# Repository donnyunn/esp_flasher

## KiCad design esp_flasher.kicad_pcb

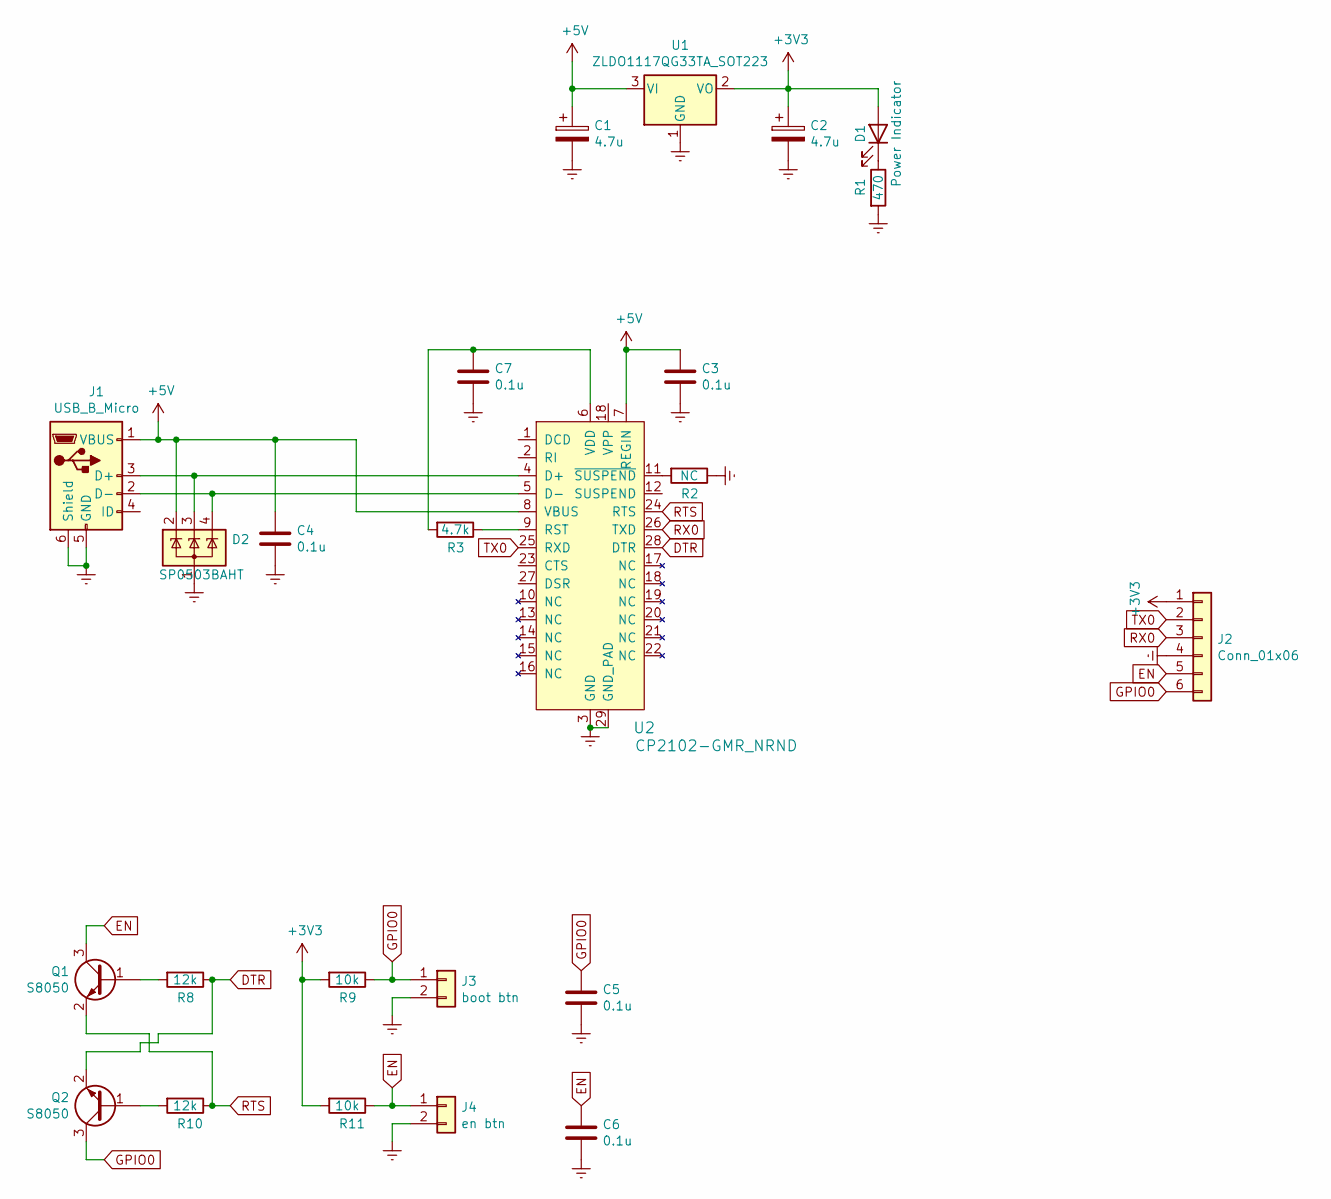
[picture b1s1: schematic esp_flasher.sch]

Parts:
C1, C2: 4.7u; CP_EIA-3216-18_Kemet-A
C3, C4, C5, C6, C7: 0.1u; C_0603_1608Metric_Pad1.08x0.95mm_HandSolder
D1: Power Indicator; LED_0805_2012Metric_Pad1.15x1.40mm_HandSolder
D2: SP0503BAHT; SOT-143
J1: USB_B_Micro; USB_Micro-AB_Molex_47590-0001; MPN 47589-0001
J2: Conn_01x06; JST_PH_B6B-PH-K_1x06_P2.00mm_Vertical
J3: boot btn; SW_SPST_EVQPE1
J4: en btn; SW_SPST_EVQPE1
Q1, Q2: S8050; SOT-23; MPN S8050
R1: 470; R_0603_1608Metric_Pad0.98x0.95mm_HandSolder
R2: NC; R_0603_1608Metric_Pad0.98x0.95mm_HandSolder
R3: 4.7k; R_0603_1608Metric_Pad0.98x0.95mm_HandSolder
R8, R10: 12k; R_0603_1608Metric_Pad0.98x0.95mm_HandSolder
R9, R11: 10k; R_0603_1608Metric_Pad0.98x0.95mm_HandSolder
U1: ZLDO1117QG33TA_SOT223; SOT-223-3_TabPin2; MPN ZLDO1117QG33TA
U2: CP2102-GMR_NRND; VFQFN-28-1EP_5x5mm; MPN CP2102-GMR; Digi-Key_PN 336-1160-1-ND

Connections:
+3V3: C2.1, D1.2 (A), J2.1, R9.2, R11.2, U1.2 (VO)
+5V: C1.1, C3.1, C4.1, D2.2 (K), J1.1 (VBUS), U1.3 (VI), U2.7 (REGIN), U2.8 (VBUS)
DTR: Q2.2 (E), R8.1, U2.28 (DTR)
EN: C6.1, J2.5, J4.1, Q1.3 (C), R11.1
Earth: C1.2, C2.2, C3.2, C4.2, C5.2, C6.2, C7.2, D2.1 (A), J1.5 (GND), J1.6 (Shield), J2.4, J3.2, J4.2, R1.2, R2.1, U1.1 (GND), U2.3 (GND), U2.29 (GND_PAD)
GPIO0: C5.1, J2.6, J3.1, Q2.3 (C), R9.1
unnamed: C7.1, R3.2, U2.6 (VDD)
unnamed: D1.1 (K), R1.1
unnamed: D2.3 (K), J1.3 (D+), U2.4 (D+)
unnamed: D2.4 (K), J1.2 (D-), U2.5 (D-)
unnamed: Q1.1 (B), R8.2
unnamed: Q2.1 (B), R10.2
unnamed: R2.2, U2.11 (~SUSPEND)
unnamed: R3.1, U2.9 (RST)
RTS: Q1.2 (E), R10.1, U2.24 (RTS)
RX0: J2.3, U2.26 (TXD)
TX0: J2.2, U2.25 (RXD)

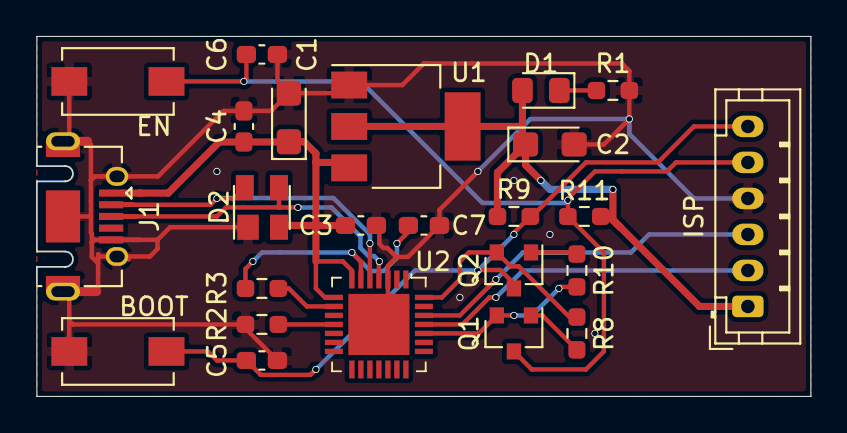
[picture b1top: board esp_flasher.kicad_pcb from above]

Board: 2 copper layers, 43.0 x 19.9 mm, 24 parts (0 on the bottom side), 17 nets.

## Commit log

2021-07-20 2021-07-20
2021-07-20 2021-07-20 2
